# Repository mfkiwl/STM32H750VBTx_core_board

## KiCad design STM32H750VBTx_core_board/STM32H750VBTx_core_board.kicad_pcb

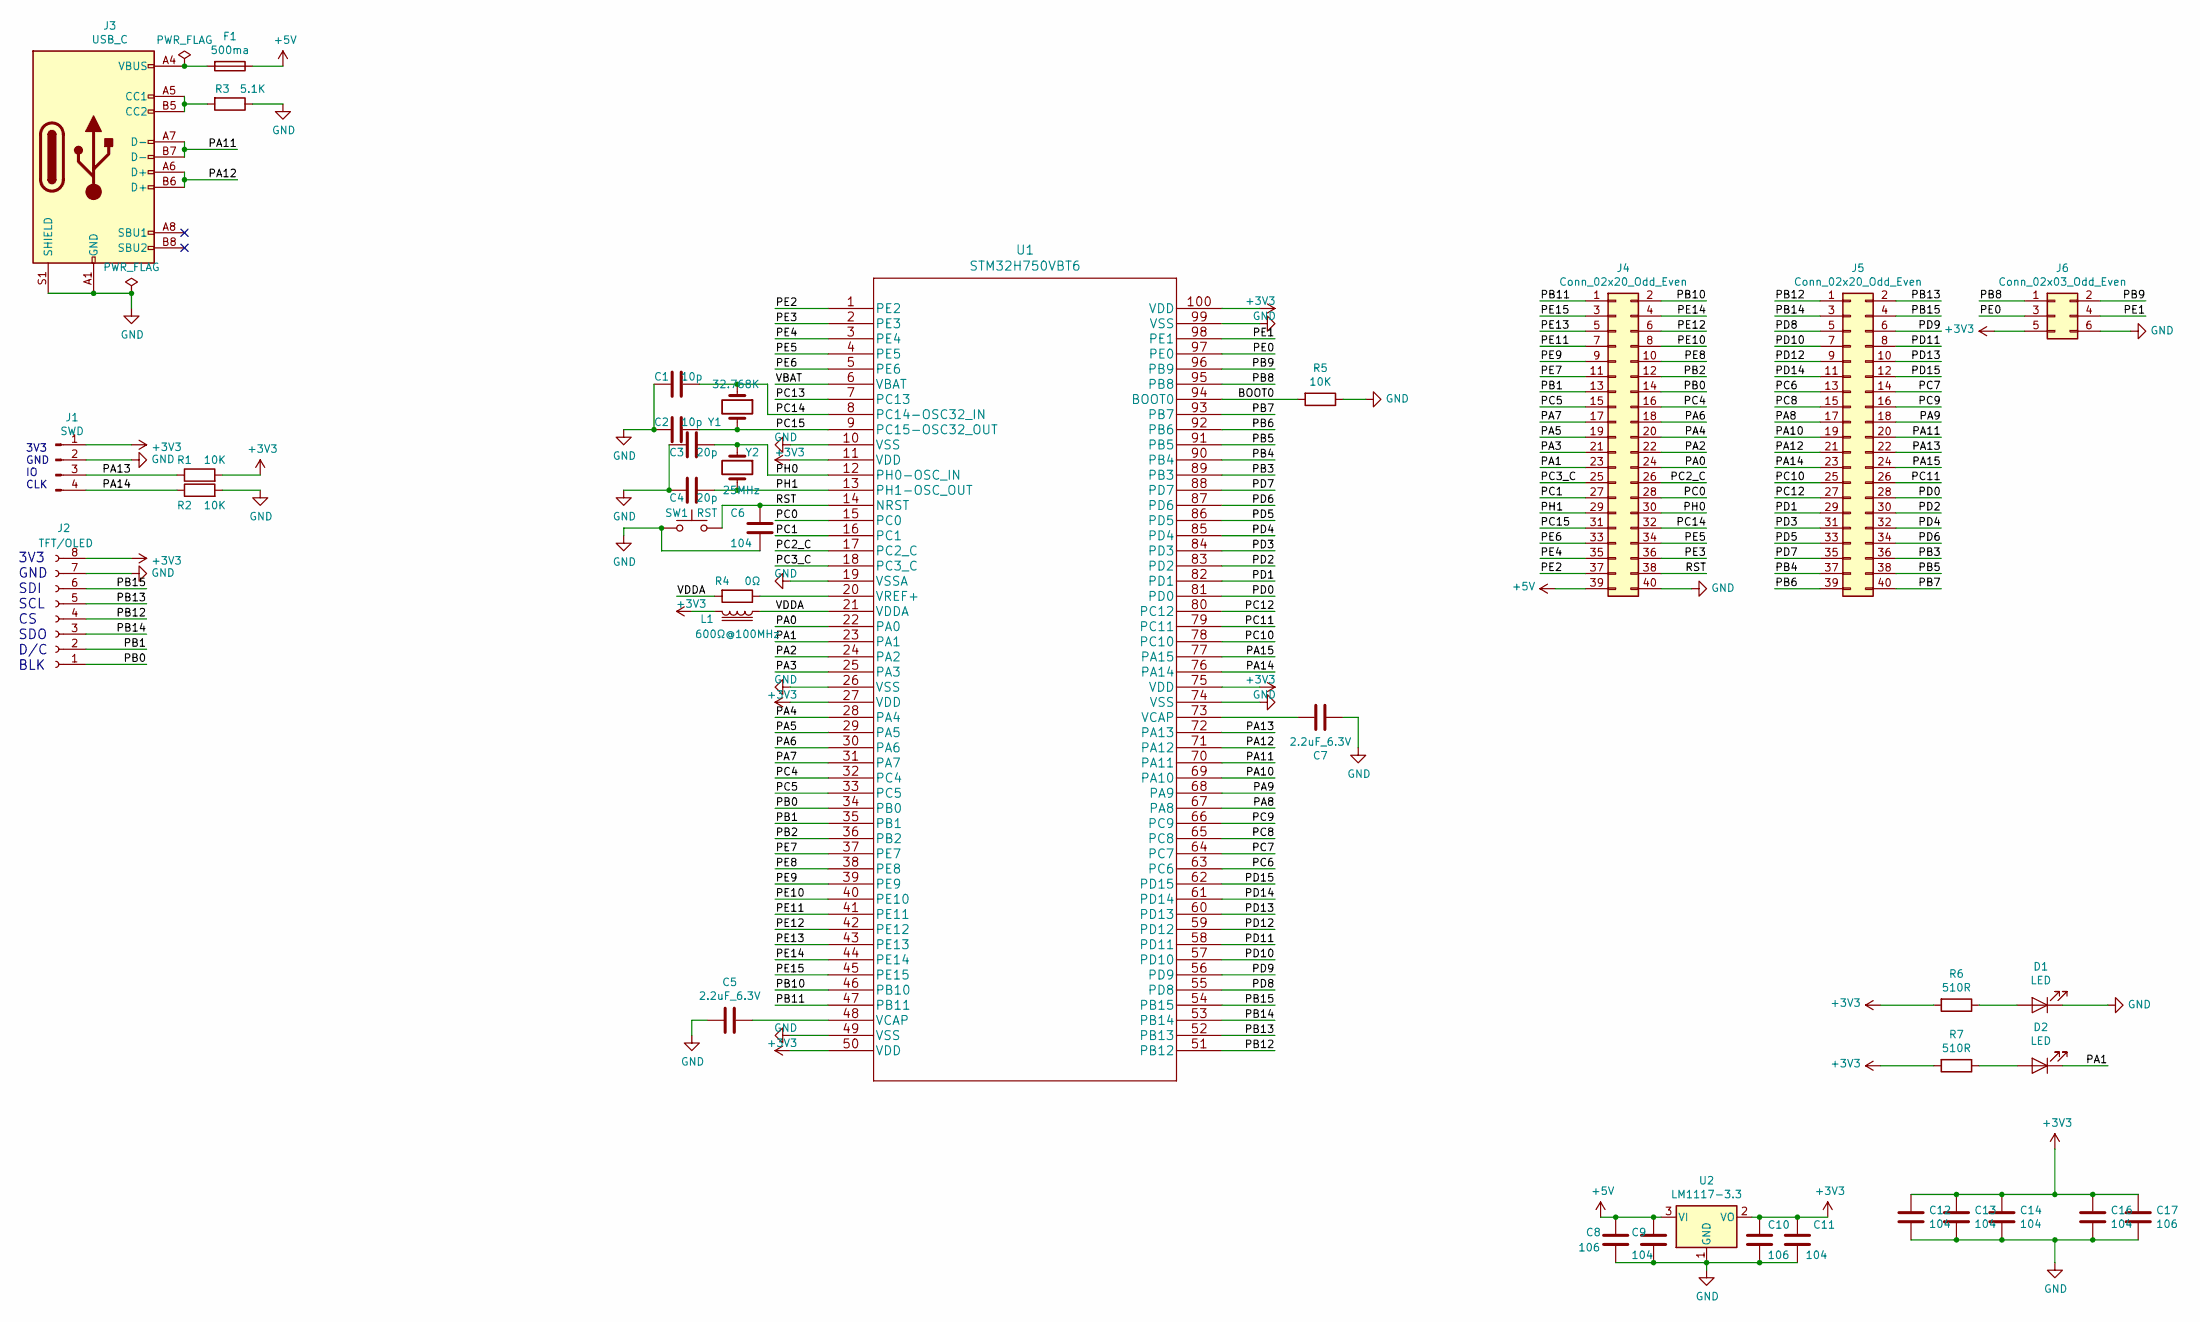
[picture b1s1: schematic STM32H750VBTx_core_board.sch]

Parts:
C1, C2: 10p; C_0603_1608Metric
C3, C4: 20p; C_0603_1608Metric
C5, C7: 2.2uF_6.3V; C_0603_1608Metric
C6, C9, C11, C12, C13, C14, C16: 104; C_0603_1608Metric
C8, C10, C17: 106; C_0603_1608Metric
D1, D2: LED; LED_0603_1608Metric
F1: 500ma; Fuse_1206_3216Metric
J1: SWD; PinHeader_1x04_P2.54mm_Vertical
J2: TFT/OLED; PinSocket_1x08_P2.54mm_Vertical
J3: USB_C; USB_C_Receptacle_HRO_TYPE-C-31-M-12
J4, J5: Conn_02x20_Odd_Even; PinHeader_2x20_P2.54mm_Vertical
J6: Conn_02x03_Odd_Even; PinHeader_2x03_P2.54mm_Vertical
L1: 600Ω@100MHz; L_0603_1608Metric
R1, R2, R5: 10K; R_0603_1608Metric
R3: 5.1K; R_0603_1608Metric
R4: 0Ω; R_0603_1608Metric
R6, R7: 510R; R_0603_1608Metric
SW1: RST; SW_SPST_EVPBF
U1: STM32H750VBT6; LQFP-100_14x14mm_P0.5mm
U2: LM1117-3.3; SOT-223
Y1: 32.768K; Crystal_AT310_D3.0mm_L10.0mm_Horizontal
Y2: 25MHz; Crystal_HC49-4H_Vertical

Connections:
+3V3: C10.1, C11.1, C12.1, C13.1, C14.1, C16.1, C17.1, J1.1, J2.8, J6.5, L1.2, R1.2, R6.2, R7.2, U1.11 (VDD), U1.27 (VDD), U1.50 (VDD), U1.75 (VDD), U1.100 (VDD), U2.2 (VO)
+5V: C8.1, C9.1, F1.1, J4.39, U2.3 (VI)
/BOOT0: R5.2, U1.94 (BOOT0)
/PA0: J4.24, U1.22 (PA0)
/PA1: D2.1 (K), J4.23, U1.23 (PA1)
/PA2: J4.22, U1.24 (PA2)
/PA3: J4.21, U1.25 (PA3)
/PA4: J4.20, U1.28 (PA4)
/PA5: J4.19, U1.29 (PA5)
/PA6: J4.18, U1.30 (PA6)
/PA7: J4.17, U1.31 (PA7)
/PA8: J5.17, U1.67 (PA8)
/PA9: J5.18, U1.68 (PA9)
/PA10: J5.19, U1.69 (PA10)
/PA11: J3.A7 (D-), J3.B7 (D-), J5.20, U1.70 (PA11)
/PA12: J3.A6 (D+), J3.B6 (D+), J5.21, U1.71 (PA12)
/PA13: J1.3, J5.22, R1.1, U1.72 (PA13)
/PA14: J1.4, J5.23, R2.1, U1.76 (PA14)
/PA15: J5.24, U1.77 (PA15)
/PB0: J2.1, J4.14, U1.34 (PB0)
/PB1: J2.2, J4.13, U1.35 (PB1)
/PB2: J4.12, U1.36 (PB2)
/PB3: J5.36, U1.89 (PB3)
/PB4: J5.37, U1.90 (PB4)
/PB5: J5.38, U1.91 (PB5)
/PB6: J5.39, U1.92 (PB6)
/PB7: J5.40, U1.93 (PB7)
/PB8: J6.1, U1.95 (PB8)
/PB9: J6.2, U1.96 (PB9)
/PB10: J4.2, U1.46 (PB10)
/PB11: J4.1, U1.47 (PB11)
/PB12: J2.4, J5.1, U1.51 (PB12)
/PB13: J2.5, J5.2, U1.52 (PB13)
/PB14: J2.3, J5.3, U1.53 (PB14)
/PB15: J2.6, J5.4, U1.54 (PB15)
/PC0: J4.28, U1.15 (PC0)
/PC1: J4.27, U1.16 (PC1)
/PC2_C: J4.26, U1.17 (PC2_C)
/PC3_C: J4.25, U1.18 (PC3_C)
/PC4: J4.16, U1.32 (PC4)
/PC5: J4.15, U1.33 (PC5)
/PC6: J5.13, U1.63 (PC6)
/PC7: J5.14, U1.64 (PC7)
/PC8: J5.15, U1.65 (PC8)
/PC9: J5.16, U1.66 (PC9)
/PC10: J5.25, U1.78 (PC10)
/PC11: J5.26, U1.79 (PC11)
/PC12: J5.27, U1.80 (PC12)
/PC13: U1.7 (PC13)
/PC14: C1.1, J4.32, U1.8 (PC14-OSC32_IN), Y1.1
/PC15: C2.1, J4.31, U1.9 (PC15-OSC32_OUT), Y1.2
/PD0: J5.28, U1.81 (PD0)
/PD1: J5.29, U1.82 (PD1)
/PD2: J5.30, U1.83 (PD2)
/PD3: J5.31, U1.84 (PD3)
/PD4: J5.32, U1.85 (PD4)
/PD5: J5.33, U1.86 (PD5)
/PD6: J5.34, U1.87 (PD6)
/PD7: J5.35, U1.88 (PD7)
/PD8: J5.5, U1.55 (PD8)
/PD9: J5.6, U1.56 (PD9)
/PD10: J5.7, U1.57 (PD10)
/PD11: J5.8, U1.58 (PD11)
/PD12: J5.9, U1.59 (PD12)
/PD13: J5.10, U1.60 (PD13)
/PD14: J5.11, U1.61 (PD14)
/PD15: J5.12, U1.62 (PD15)
/PE0: J6.3, U1.97 (PE0)
/PE1: J6.4, U1.98 (PE1)
/PE2: J4.37, U1.1 (PE2)
/PE3: J4.36, U1.2 (PE3)
/PE4: J4.35, U1.3 (PE4)
/PE5: J4.34, U1.4 (PE5)
/PE6: J4.33, U1.5 (PE6)
/PE7: J4.11, U1.37 (PE7)
/PE8: J4.10, U1.38 (PE8)
/PE9: J4.9, U1.39 (PE9)
/PE10: J4.8, U1.40 (PE10)
/PE11: J4.7, U1.41 (PE11)
/PE12: J4.6, U1.42 (PE12)
/PE13: J4.5, U1.43 (PE13)
/PE14: J4.4, U1.44 (PE14)
/PE15: J4.3, U1.45 (PE15)
/PH0: C3.2, J4.30, U1.12 (PH0-OSC_IN), Y2.1
/PH1: C4.2, J4.29, U1.13 (PH1-OSC_OUT), Y2.2
/RST: C6.2, J4.38, SW1.2, U1.14 (NRST)
/VBAT: U1.6 (VBAT)
/VDDA: L1.1, R4.2, U1.21 (VDDA)
GND: C1.2, C2.2, C3.1, C4.1, C5.2, C6.1, C7.2, C8.2, C9.2, C10.2, C11.2, C12.2, C13.2, C14.2, C16.2, C17.2, D1.1 (K), J1.2, J2.7, J3.A1 (GND), J3.A12 (GND), J3.B1 (GND), J3.B12 (GND), J3.S1 (SHIELD), J4.40, J6.6, R2.2, R3.1, R5.1, SW1.1, U1.10 (VSS), U1.19 (VSSA), U1.26 (VSS), U1.49 (VSS), U1.74 (VSS), U1.99 (VSS), U2.1 (GND)
unnamed: C5.1, U1.48 (VCAP)
unnamed: C7.1, U1.73 (VCAP)
unnamed: D1.2 (A), R6.1
unnamed: D2.2 (A), R7.1
unnamed: F1.2, J3.A4 (VBUS), J3.A9 (VBUS), J3.B4 (VBUS), J3.B9 (VBUS)
unnamed: J3.A5 (CC1), J3.B5 (CC2), R3.2
unnamed: R4.1, U1.20 (VREF+)

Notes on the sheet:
3V3 GND IO CLK
3V3 GND SDI SCL CS SDO D/C BLK

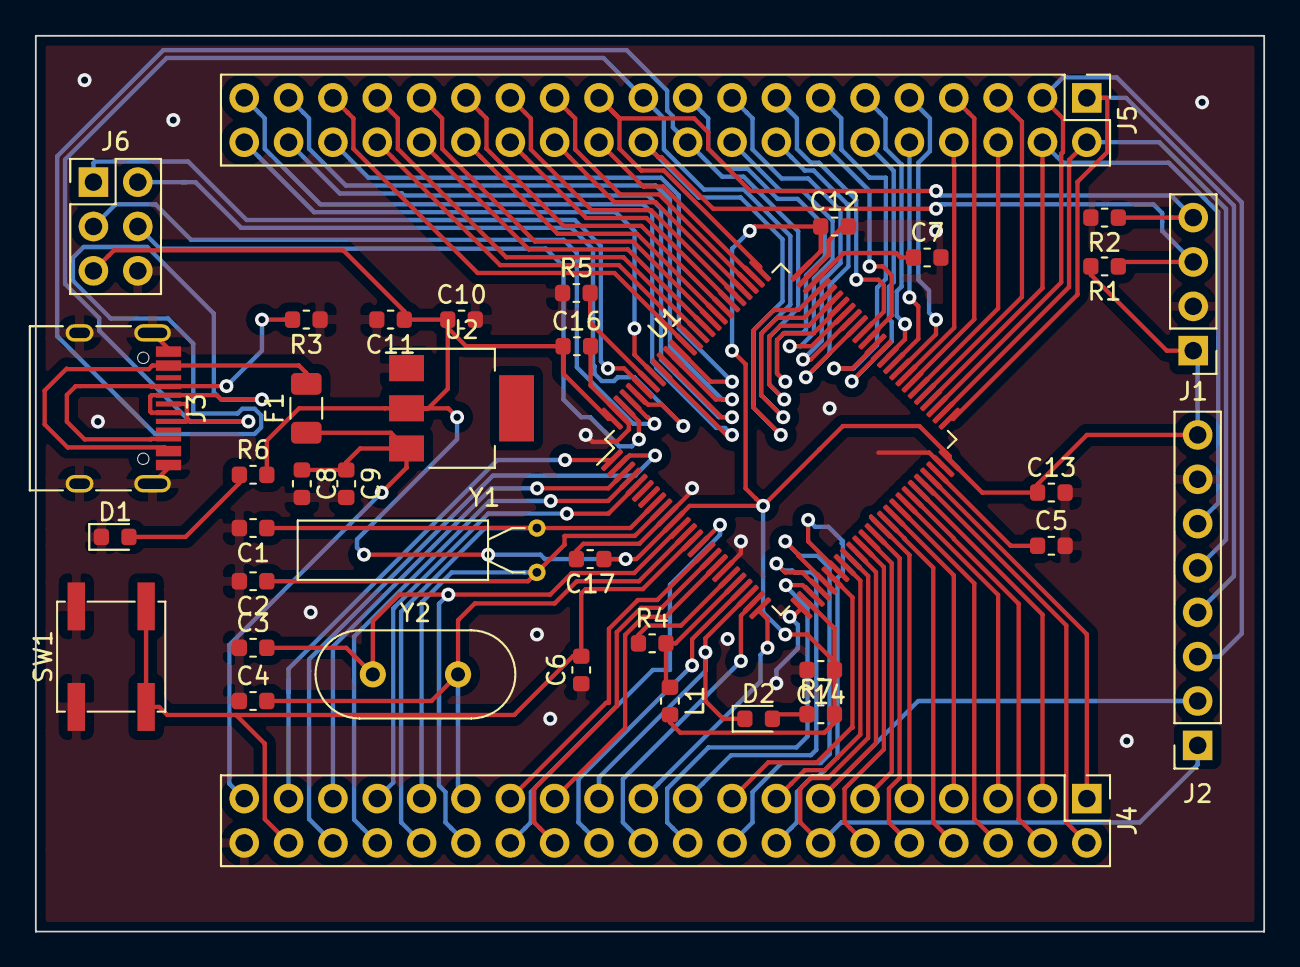
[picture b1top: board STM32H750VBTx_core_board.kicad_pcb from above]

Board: 2 copper layers, 70.4 x 51.3 mm, 38 parts (0 on the bottom side), 94 nets.
